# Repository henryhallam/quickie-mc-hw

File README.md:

SiCtroller, also known as Kittyverter, is a sensorless BLDC motor controller
capable of driving low-inductance motors at up to 20 kW.

The power stage uses the Cree/Wolfspeed/Infineon CCS050M12CM2 power module, a
six-pack of 1200V, 50A silicon carbide MOSFETs.  Three Infineon 2ED020I12-F2
dual-channel (half-bridge) gate driver ICs with desaturation fault protection
are powered by six Murata MGJ1 isolated +19V/-5V DC-DC modules.

Current feedback is provided on all three phases by Allegro ACS770 isolated
hall-effect current sensors with a full-scale range of +/-100A.  Phase voltages
are measured via potential dividers with precision RC low-pass filters.

Control is based around the Texas Instruments TMS320F28069M Piccolo DSP MCU,
using the FAST estimator in the Instaspin-FOC ROM library for motor parameter
identification and field-oriented control.

The main external interface is an isolated CAN transceiver.  Some non-isolated
GPIOs and ADC inputs are also brought to external connectors for expansion.

[1]: www.wolfspeed.com/downloads/dl/file/id/189/product/104/ccs050m12cm2.pdf

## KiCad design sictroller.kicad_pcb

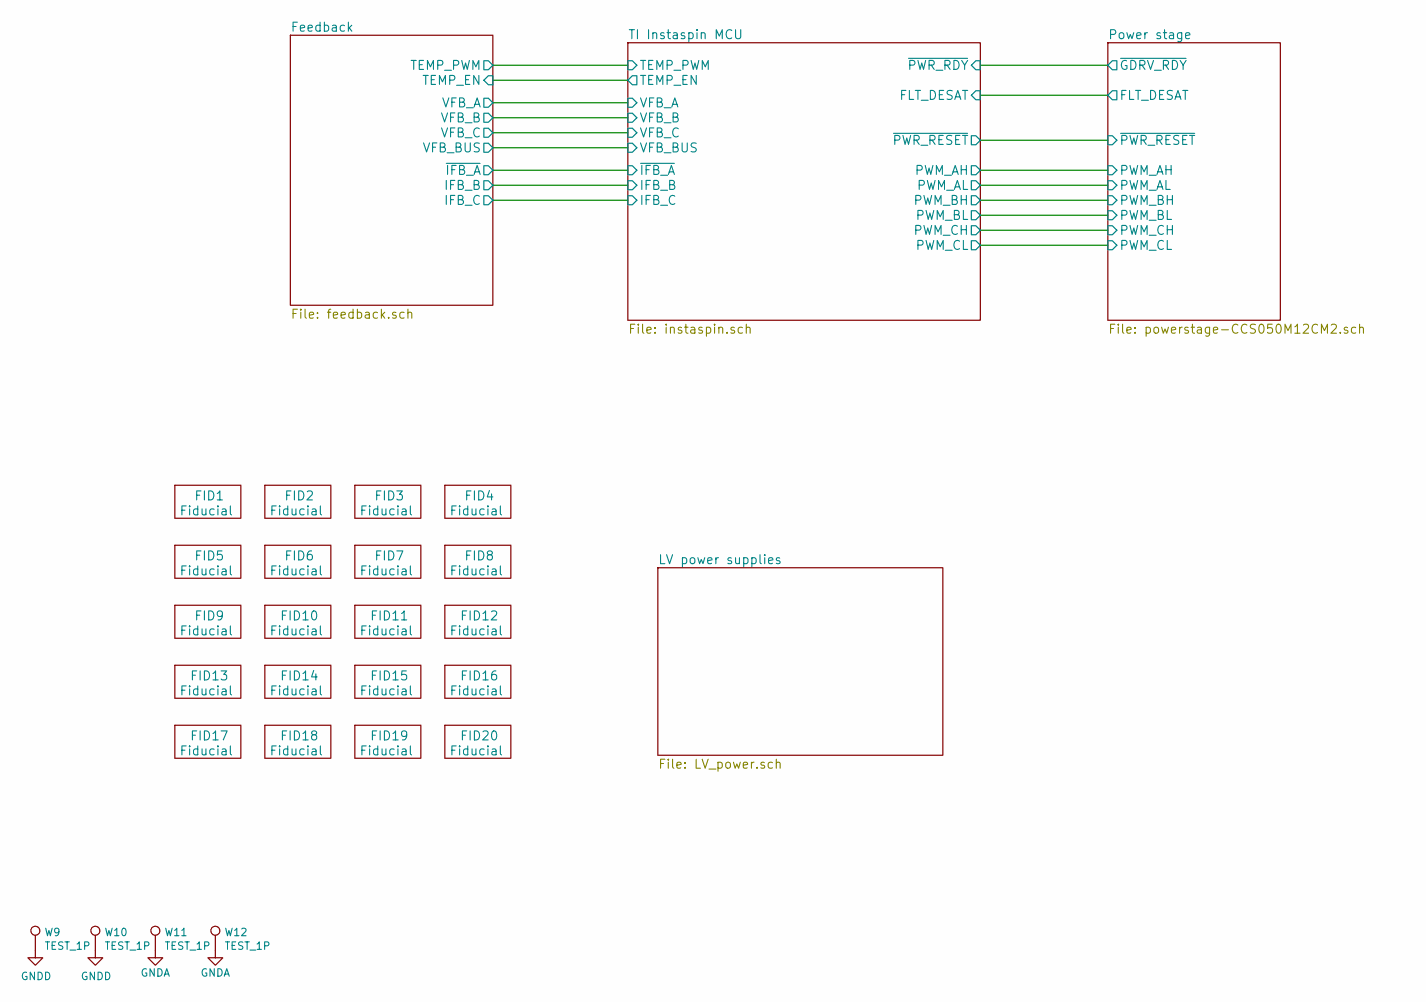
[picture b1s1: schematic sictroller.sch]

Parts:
FID1, FID2, FID3, FID4, FID5, FID6, FID7, FID8, FID9, FID10, FID11, FID12, FID13, FID14, FID15, FID16, FID17, FID18, FID19, FID20: Fiducial; Fiducial_1mm_CopperTop
W9, W10, W11, W12: TEST_1P; Measurement_Point_Round-TH_Small

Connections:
GND: W9.1, W10.1; also elsewhere on the board
GNDA: W11.1, W12.1; also elsewhere on the board

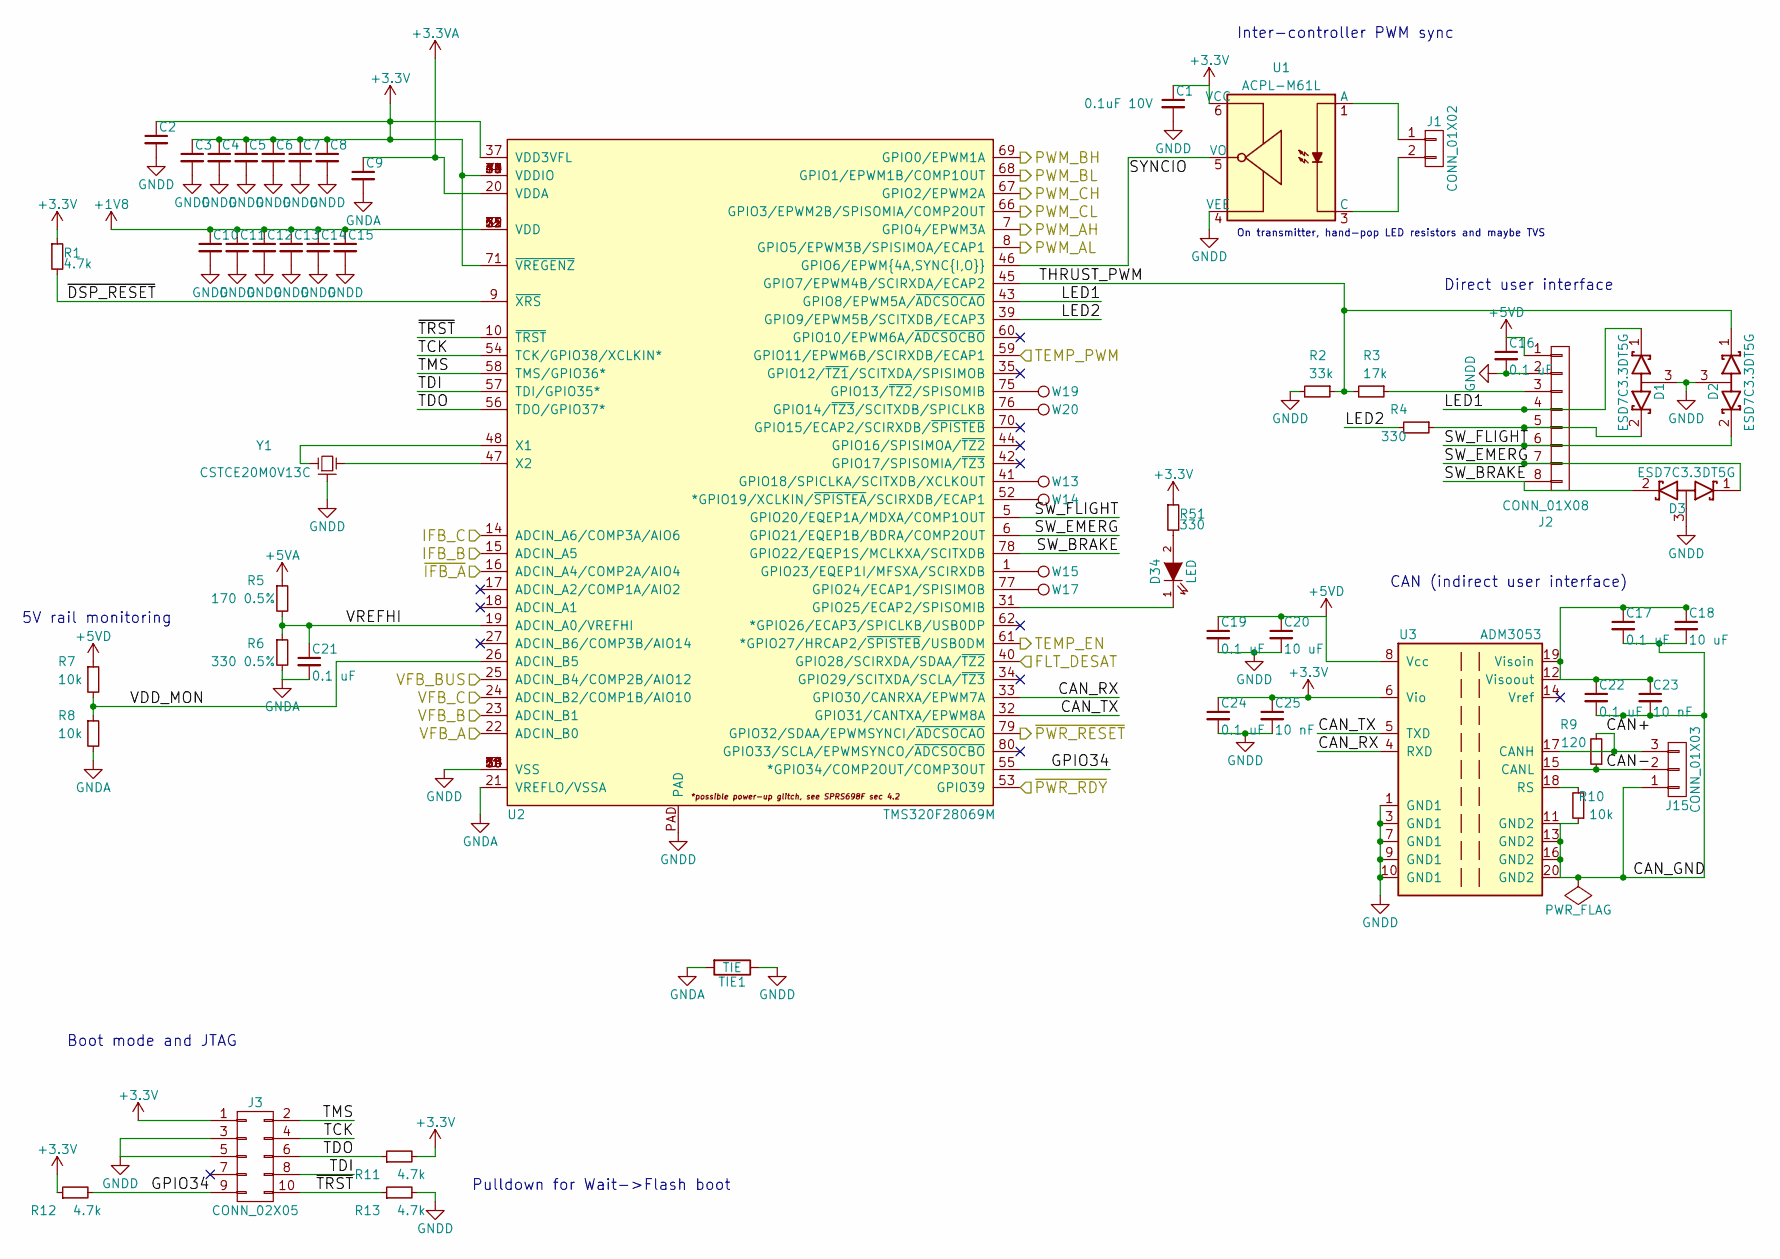
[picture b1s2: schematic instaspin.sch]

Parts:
C1: 0.1uF 10V; C_0402
C2, C3, C4, C5, C6, C7, C8, C9: 2.2uF 10V; C_0603
C10, C11, C12, C13, C14, C15: 2.2uF 6V; C_0402
C16, C17, C19, C21, C22, C24: 0.1 uF; C_0402
C18, C20: 10 uF; C_0805
C23, C25: 10 nF; C_0402
D1, D2, D3: ESD7C3.3DT5G; SOT-723
D34: LED; LED_0603
J1: CONN_01X02; Molex_PicoBlade_53261-0271
J2: CONN_01X08; Molex_PicoBlade_53261-0871
J3: CONN_02X05; FTSH-105-01-L-DV-K
J15: CONN_01X03; Molex_PicoBlade_53261-0371
R1, R11, R12, R13: 4.7k; R_0402
R2: 33k; R_0402
R3: 17k; R_0402
R4, R51: 330; R_0402
R5: 170 0.5%; R_0402
R6: 330 0.5%; R_0402
R7, R8, R10: 10k; R_0402
R9: 120; R_0805
TIE1: TIE; NetTie-_Connected_3x5
U1: ACPL-M61L; ACPL-M61L_SO-5
U2: TMS320F28069M; PFP
U3: ADM3053; SOIC-20W_7.5x12.8mm_Pitch1.27mm
W13, W14, W15, W17, W19, W20: TEST_1P; Measurement_Point_Round-TH_Small
Y1: CSTCE20M0V13C; CSTCE_V13C

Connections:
+1V8: C10.1, C11.1, C12.1, C13.1, C14.1, C15.1, U2.2 (VDD), U2.12 (VDD), U2.29 (VDD), U2.51 (VDD), U2.65 (VDD), U2.72 (VDD); also elsewhere on the board
+3.3VA: C9.1, U2.20 (VDDA); also elsewhere on the board
+3V3: C1.1, C2.1, C3.1, C4.1, C5.1, C6.1, C7.1, C8.1, C24.1, C25.1, J3.1, R1.1, R11.2, R12.1, R51.1, U1.6 (VCC), U2.4 (VDDIO), U2.11 (VDDIO), U2.30 (VDDIO), U2.37 (VDD3VFL), U2.49 (VDDIO), U2.63 (VDDIO), U2.71 (~VREGENZ), U2.74 (VDDIO), U3.6 (Vio); also elsewhere on the board
+5VA: R5.1; also elsewhere on the board
+5VD: C16.1, C19.1, C20.1, J2.1, R7.1, U3.8 (Vcc); also elsewhere on the board
/Feedback/IFB_B: U2.15 (ADCIN_A5); also elsewhere on the board
/Feedback/IFB_C: U2.14 (ADCIN_A6/COMP3A/AIO6); also elsewhere on the board
/Feedback/TEMP_EN: U2.61 (*GPIO27/HRCAP2/~SPISTEB~/USB0DM); also elsewhere on the board
/Feedback/TEMP_PWM: U2.59 (GPIO11/EPWM6B/SCIRXDB/ECAP1); also elsewhere on the board
/Feedback/VFB_A: U2.22 (ADCIN_B0); also elsewhere on the board
/Feedback/VFB_B: U2.23 (ADCIN_B1); also elsewhere on the board
/Feedback/VFB_BUS: U2.25 (ADCIN_B4/COMP2B/AIO12); also elsewhere on the board
/Feedback/VFB_C: U2.24 (ADCIN_B2/COMP1B/AIO10); also elsewhere on the board
/Feedback/~IFB_A: U2.16 (ADCIN_A4/COMP2A/AIO4); also elsewhere on the board
/Power stage/FLT_DESAT: U2.40 (GPIO28/SCIRXDA/SDAA/~TZ2); also elsewhere on the board
/Power stage/PWM_AH: U2.7 (GPIO4/EPWM3A); also elsewhere on the board
/Power stage/PWM_AL: U2.8 (GPIO5/EPWM3B/SPISIMOA/ECAP1); also elsewhere on the board
/Power stage/PWM_BH: U2.69 (GPIO0/EPWM1A); also elsewhere on the board
/Power stage/PWM_BL: U2.68 (GPIO1/EPWM1B/COMP1OUT); also elsewhere on the board
/Power stage/PWM_CH: U2.67 (GPIO2/EPWM2A); also elsewhere on the board
/Power stage/PWM_CL: U2.66 (GPIO3/EPWM2B/SPISOMIA/COMP2OUT); also elsewhere on the board
/Power stage/~GDRV_RDY: U2.53 (GPIO39); also elsewhere on the board
/Power stage/~PWR_RESET: U2.79 (GPIO32/SDAA/EPWMSYNCI/~ADCSOCAO); also elsewhere on the board
/TI Instaspin MCU/CAN+: J15.3, R9.2, U3.17 (CANH)
/TI Instaspin MCU/CAN-: J15.2, R9.1, U3.15 (CANL)
/TI Instaspin MCU/CAN_GND: C17.2, C18.2, C22.2, C23.2, J15.1, R10.1, U3.11 (GND2), U3.13 (GND2), U3.16 (GND2), U3.20 (GND2)
/TI Instaspin MCU/CAN_RX: U2.33 (GPIO30/CANRXA/EPWM7A), U3.4 (RXD)
/TI Instaspin MCU/CAN_TX: U2.32 (GPIO31/CANTXA/EPWM8A), U3.5 (TXD)
/TI Instaspin MCU/GPIO34: J3.9, R12.2, U2.55 (*GPIO34/COMP2OUT/COMP3OUT)
/TI Instaspin MCU/LED1: D1.1 (K), J2.4, U2.43 (GPIO8/EPWM5A/~ADCSOCAO)
/TI Instaspin MCU/LED2: R4.2, U2.39 (GPIO9/EPWM5B/SCITXDB/ECAP3)
/TI Instaspin MCU/SW_BRAKE: D3.2 (K), J2.8, U2.78 (GPIO22/EQEP1S/MCLKXA/SCITXDB)
/TI Instaspin MCU/SW_EMERG: D3.1 (K), J2.7, U2.6 (GPIO21/EQEP1B/BDRA/COMP2OUT)
/TI Instaspin MCU/SW_FLIGHT: D2.2 (K), J2.6, U2.5 (GPIO20/EQEP1A/MDXA/COMP1OUT)
/TI Instaspin MCU/SYNCIO: U1.5 (VO), U2.46 (GPIO6/EPWM{4A,SYNC{I,O}})
/TI Instaspin MCU/TCK: J3.4, U2.54 (TCK/GPIO38/XCLKIN*)
/TI Instaspin MCU/TDI: J3.8, U2.57 (TDI/GPIO35*)
/TI Instaspin MCU/TDO: J3.6, R11.1, U2.56 (TDO/GPIO37*)
/TI Instaspin MCU/THRUST_PWM: D2.1 (K), R2.1, R3.2, U2.45 (GPIO7/EPWM4B/SCIRXDA/ECAP2)
/TI Instaspin MCU/TMS: J3.2, U2.58 (TMS/GPIO36*)
/TI Instaspin MCU/VDD_MON: R7.2, R8.1, U2.26 (ADCIN_B5)
/TI Instaspin MCU/VREFHI: C21.1, R5.2, R6.1, U2.19 (ADCIN_A0/VREFHI)
/TI Instaspin MCU/~DSP_RESET: R1.2, U2.9 (~XRS)
/TI Instaspin MCU/~TRST: J3.10, R13.1, U2.10 (~TRST)
GND: C1.2, C2.2, C3.2, C4.2, C5.2, C6.2, C7.2, C8.2, C10.2, C11.2, C12.2, C13.2, C14.2, C15.2, C16.2, C19.2, C20.2, C24.2, C25.2, D1.3 (A), D2.3 (A), D3.3 (A), J2.2, J3.3, J3.5, R2.2, R13.2, TIE1.1, U1.4 (VEE), U2.3 (VSS), U2.13 (VSS), U2.28 (VSS), U2.38 (VSS), U2.50 (VSS), U2.64 (VSS), U2.73 (VSS), U2.PAD, U3.1 (GND1), U3.3 (GND1), U3.7 (GND1), U3.9 (GND1), U3.10 (GND1), Y1.2 (common); also elsewhere on the board
GNDA: C9.2, C21.2, R6.2, R8.2, TIE1.2, U2.21 (VREFLO/VSSA); also elsewhere on the board
unnamed: C17.1, C18.1, C22.1, C23.1, U3.12 (Visoout), U3.19 (Visoin)
unnamed: D1.2 (K), J2.5, R4.1
unnamed: D34.1 (K), U2.31 (GPIO25/ECAP2/SPISOMIB)
unnamed: D34.2 (A), R51.2
unnamed: J1.1, U1.1 (A)
unnamed: J1.2, U1.3 (C)
unnamed: J2.3, R3.1
unnamed: R10.2, U3.18 (RS)
unnamed: U2.1 (GPIO23/EQEP1I/MFSXA/SCIRXDB), W15.1
unnamed: U2.41 (GPIO18/SPICLKA/SCITXDB/XCLKOUT), W13.1
unnamed: U2.47 (X2), Y1.3 (2)
unnamed: U2.48 (X1), Y1.1
unnamed: U2.52 (*GPIO19/XCLKIN/~SPISTEA~/SCIRXDB/ECAP1), W14.1
unnamed: U2.75 (GPIO13/~TZ2~/SPISOMIB), W19.1
unnamed: U2.76 (GPIO14/~TZ3~/SCITXDB/SPICLKB), W20.1
unnamed: U2.77 (GPIO24/ECAP1/SPISIMOB), W17.1

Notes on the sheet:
Boot mode and JTAG
On transmitter, hand-pop LED resistors and maybe TVS
Inter-controller PWM sync
Direct user interface
CAN (indirect user interface)
5V rail monitoring
Pulldown for Wait->Flash boot

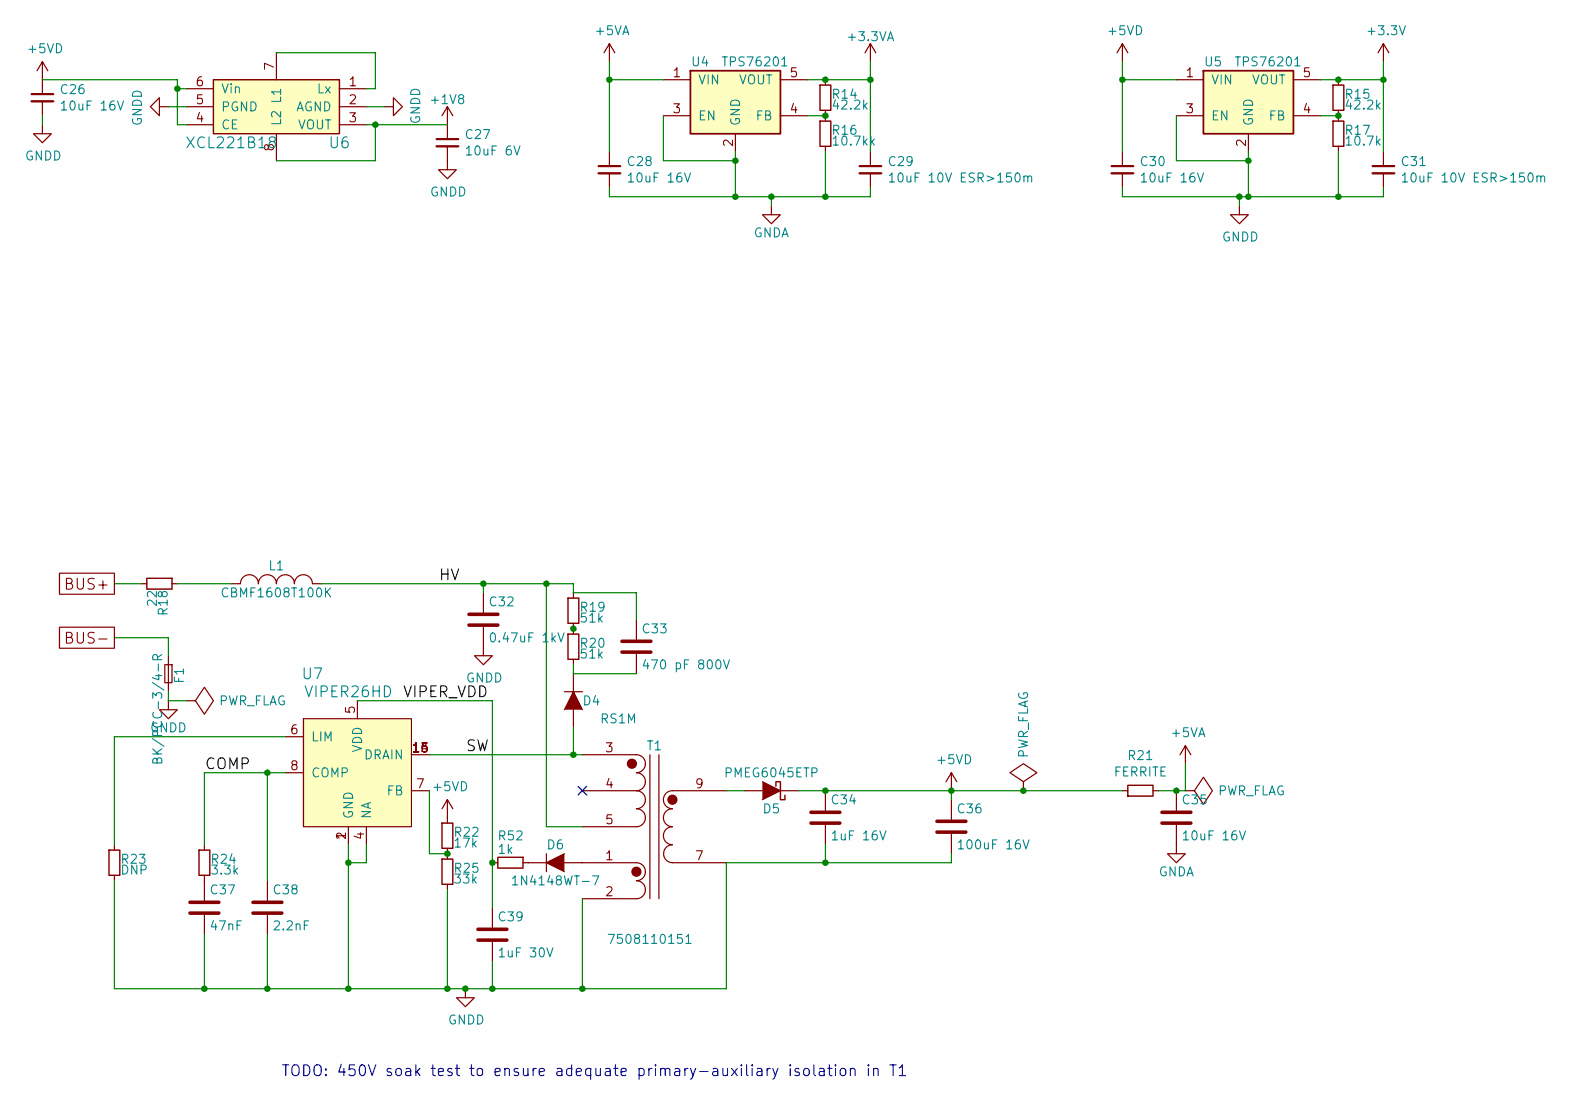
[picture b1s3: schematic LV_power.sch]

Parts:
C26, C28, C30, C35: 10uF 16V; C_0805
C27: 10uF 6V; C_0603
C29, C31: 10uF 10V ESR>150m; C_0603
C32: 0.47uF 1kV; C_2220
C33: 470 pF 800V; C_1206
C34: 1uF 16V; C_0603
C36: 100uF 16V; C_6x5
C37: 47nF; C_0402
C38: 2.2nF; C_0402
C39: 1uF 30V; C_0603
D4: RS1M; SMA_Standard
D5: PMEG6045ETP; SOD-128
D6: 1N4148WT-7; SOD-523
F1: BK/PCC-3/4-R; Fuse_TE5_Littlefuse-395Series
L1: CBMF1608T100K; R_0603
R14, R15: 42.2k; R_0402
R16: 10.7kk; R_0402
R17: 10.7k; R_0402
R18: 22; R_0603
R19, R20: 51k; R_1206
R21: FERRITE; R_0805
R22: 17k; R_0402
R23: DNP; R_0402
R24: 3.3k; R_0402
R25: 33k; R_0402
R52: 1k; R_0402
T1: 7508110151; WE-7508110151
U4, U5: TPS76201; SOT-23-5
U6: XCL221B18; XCL22x
U7: VIPER26HD; SOIC-16_3.9x9.9mm_Pitch1.27mm

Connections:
+1V8: C27.1, U6.3 (VOUT), U6.8 (L2); also elsewhere on the board
+3.3VA: C29.1, R14.1, U4.5 (VOUT); also elsewhere on the board
+3V3: C31.1, R15.1, U5.5 (VOUT); also elsewhere on the board
+5VA: C28.1, C35.1, R21.2, U4.1 (VIN); also elsewhere on the board
+5VD: C26.1, C30.1, C34.1, C36.1, D5.1 (K), R21.1, R22.1, U5.1 (VIN), U6.4 (CE), U6.6 (Vin); also elsewhere on the board
/LV power supplies/COMP: C38.1, R24.1, U7.8 (COMP)
/LV power supplies/HV: C32.1, C33.1, L1.2, R19.1, T1.5 (PR2)
/LV power supplies/SW: D4.2 (A), T1.3 (PR1), U7.13 (DRAIN), U7.14 (DRAIN), U7.15 (DRAIN), U7.16 (DRAIN)
/LV power supplies/VIPER_VDD: C39.1, R52.2, U7.5 (VDD)
BUS+: R18.2; also elsewhere on the board
BUS-: F1.1; also elsewhere on the board
GND: C26.2, C27.2, C30.2, C31.2, C32.2, C34.2, C36.2, C37.2, C38.2, C39.2, F1.2, R17.2, R23.2, R25.2, T1.2 (AUX2), T1.7 (S1), U5.2 (GND), U5.3 (EN), U6.2 (AGND), U6.5 (PGND), U6.PAD, U7.1 (GND), U7.2 (GND), U7.4 (NA); also elsewhere on the board
GNDA: C28.2, C29.2, C35.2, R16.2, U4.2 (GND), U4.3 (EN); also elsewhere on the board
unnamed: C33.2, D4.1 (K), R20.2
unnamed: C37.1, R24.2
unnamed: D5.2 (A), T1.9 (S2)
unnamed: D6.1 (K), R52.1
unnamed: D6.2 (A), T1.1 (AUX1)
unnamed: L1.1, R18.1
unnamed: R14.2, R16.1, U4.4 (FB)
unnamed: R15.2, R17.1, U5.4 (FB)
unnamed: R19.2, R20.1
unnamed: R22.2, R25.1, U7.7 (FB)
unnamed: R23.1, U7.6 (LIM)
unnamed: U6.1 (Lx), U6.7 (L1)

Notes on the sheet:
TODO: 450V soak test to ensure adequate primary-auxiliary isolation in T1

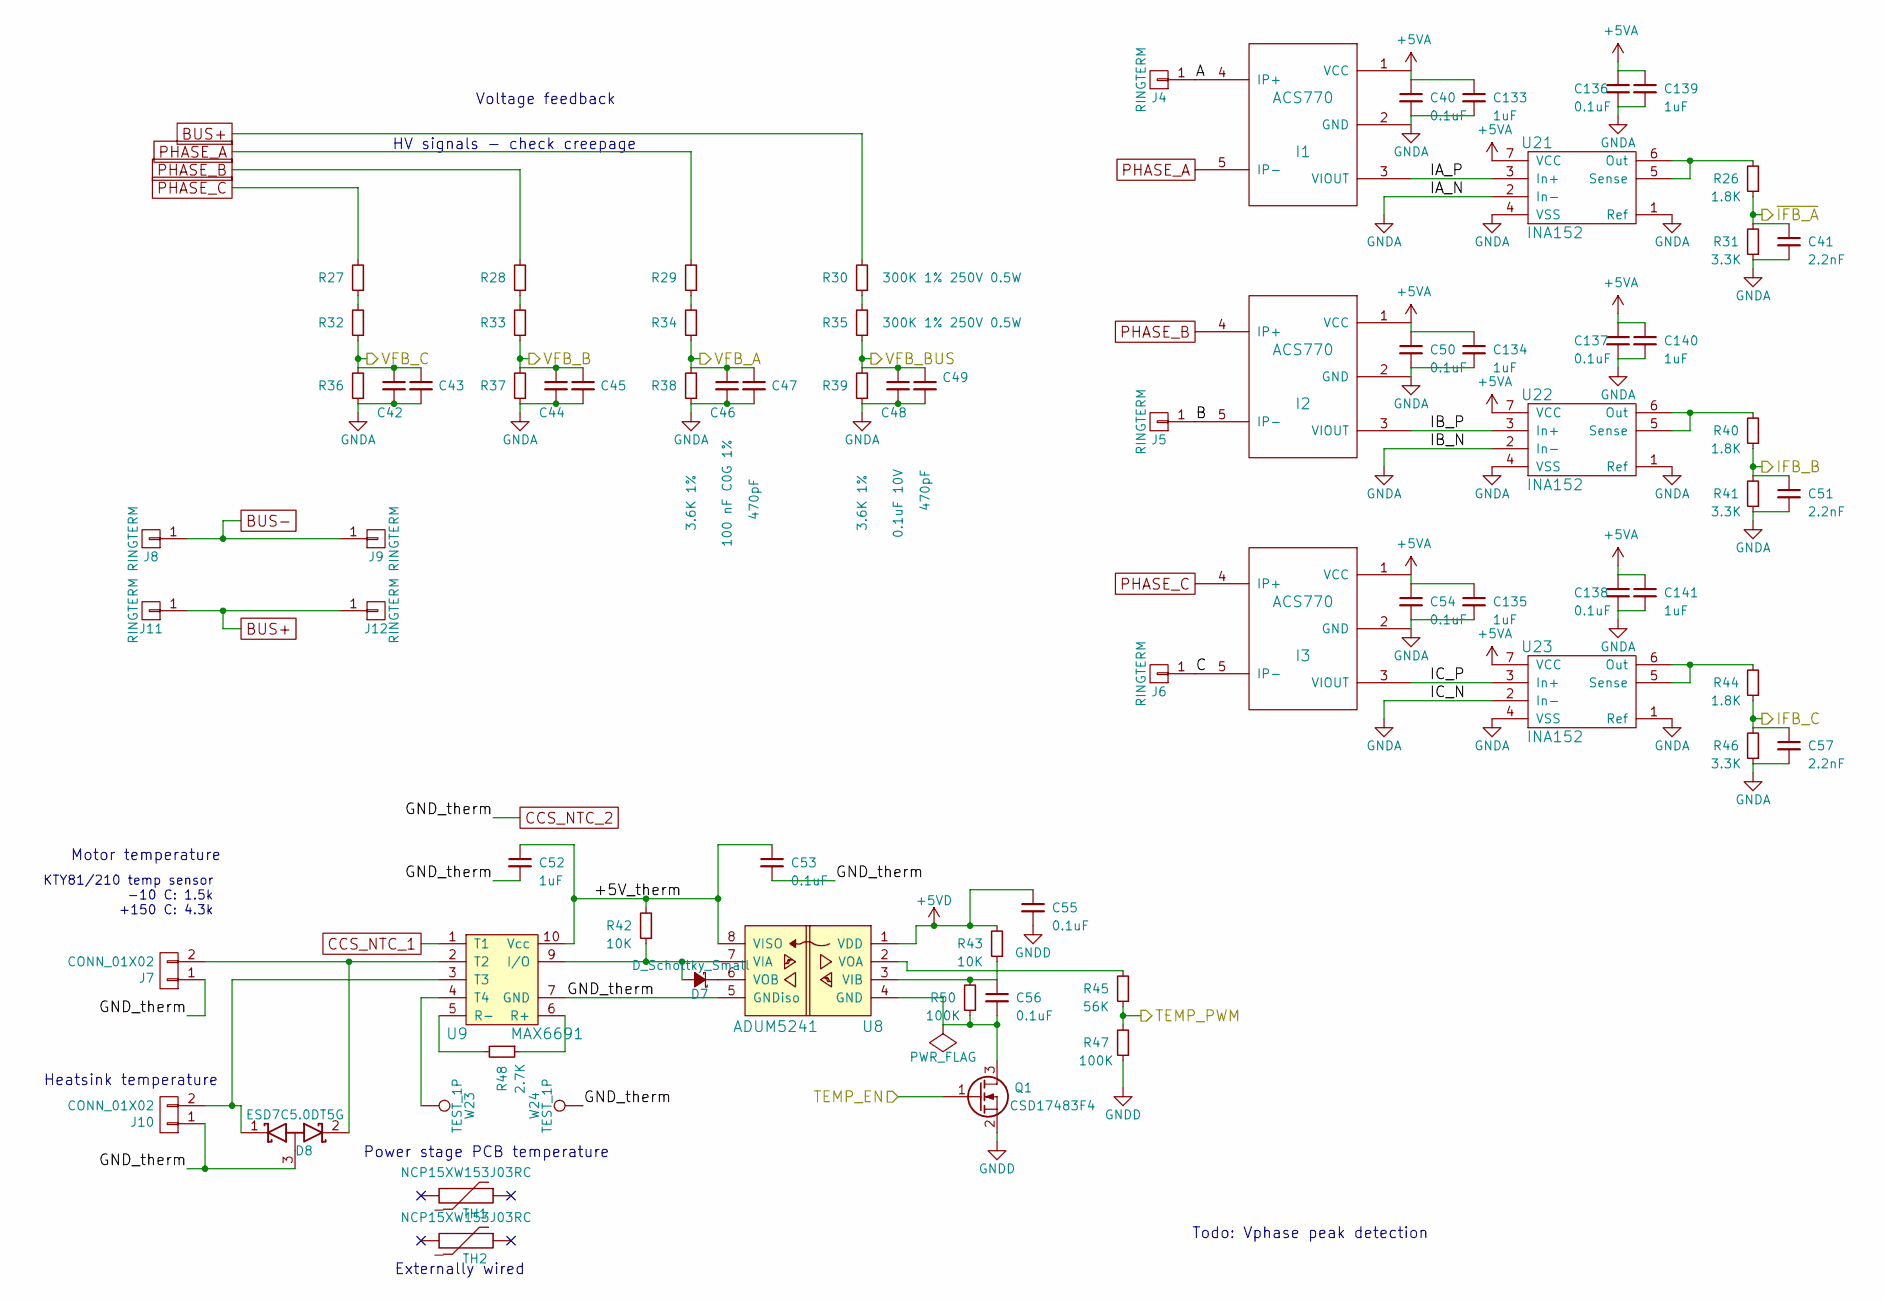
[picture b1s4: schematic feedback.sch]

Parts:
C40, C50, C53, C54, C55, C56, C136, C137, C138: 0.1uF; C_0402
C41, C51, C57: 2.2nF; C_0402
C42, C44, C46: 100 nF C0G 1%; C_1210
C43, C45, C47, C49: 470pF; C_0402
C48: 0.1uF 10V; C_0402
C52, C133, C134, C135, C139, C140, C141: 1uF; C_0603
D7: D_Schottky_Small; SOD-523
D8: ESD7C5.0DT5G; SOT-723
I1, I2, I3: ACS770
J4, J5, J6, J8, J9, J11, J12: RINGTERM; B6A-PCB
J7, J10: CONN_01X02; Molex_PicoBlade_53261-0271
Q1: CSD17483F4; FEMTOFET_YJC_YJJ
R26, R40, R44: 1.8K; R_0402
R27, R28, R29, R30, R32, R33, R34, R35: 300K 1% 250V 0.5W; R_0805
R31, R41, R46: 3.3K; R_0402
R36, R37, R38, R39: 3.6K 1%; R_0402
R42, R43: 10K; R_0402
R45: 56K; R_0402
R47, R50: 100K; R_0402
R48: 2.7K; R_0402
TH1, TH2: NCP15XW153J03RC; R_0402_extwire
U8: ADUM5241; SOIC-8_3.9x4.9mm_Pitch1.27mm
U9: MAX6691; MSOP-10_3x3mm_Pitch0.5mm
U21, U22, U23: INA152; MSOP-8_3x3mm_Pitch0.65mm
W23, W24: TEST_1P; Measurement_Point_Round-TH_Small

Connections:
+5VA: C40.1, C50.1, C54.1, C133.1, C134.1, C135.1, C136.1, C137.1, C138.1, C139.1, C140.1, C141.1, I1.1 (VCC), I2.1 (VCC), I3.1 (VCC), U21.7 (VCC), U22.7 (VCC), U23.7 (VCC); also elsewhere on the board
+5VD: C55.1, R43.2, U8.1 (VDD); also elsewhere on the board
/Feedback/+5V_therm: C52.1, C53.1, R42.2, U8.8 (VISO), U9.10 (Vcc)
/Feedback/A: I1.4 (IP+), J4.1
/Feedback/B: I2.5 (IP-), J5.1
/Feedback/C: I3.5 (IP-), J6.1
/Feedback/IA_P: I1.3 (VIOUT), U21.3 (In+)
/Feedback/IB_P: I2.3 (VIOUT), U22.3 (In+)
/Feedback/IC_P: I3.3 (VIOUT), U23.3 (In+)
/Feedback/IFB_B: C51.1, R40.1, R41.2; also elsewhere on the board
/Feedback/IFB_C: C57.1, R44.1, R46.2; also elsewhere on the board
/Feedback/TEMP_EN: Q1.1 (G); also elsewhere on the board
/Feedback/TEMP_PWM: R45.1, R47.2; also elsewhere on the board
/Feedback/VFB_A: C46.1, C47.1, R34.1, R38.2; also elsewhere on the board
/Feedback/VFB_B: C44.1, C45.1, R33.1, R37.2; also elsewhere on the board
/Feedback/VFB_BUS: C48.1, C49.1, R35.1, R39.2; also elsewhere on the board
/Feedback/VFB_C: C42.1, C43.1, R32.1, R36.2; also elsewhere on the board
/Feedback/~IFB_A: C41.1, R26.1, R31.2; also elsewhere on the board
BUS+: J11.1, J12.1, R30.2; also elsewhere on the board
BUS-: J8.1, J9.1; also elsewhere on the board
CCS_NTC_1: U9.1 (T1); also elsewhere on the board
CCS_NTC_2: C52.2, C53.2, D8.3 (A), J7.1, J10.1, U8.5 (GNDiso), U9.7 (GND), W24.1; also elsewhere on the board
GND: C55.2, Q1.2 (S), R47.1; also elsewhere on the board
GNDA: C40.2, C41.2, C42.2, C43.2, C44.2, C45.2, C46.2, C47.2, C48.2, C49.2, C50.2, C51.2, C54.2, C57.2, C133.2, C134.2, C135.2, C136.2, C137.2, C138.2, C139.2, C140.2, C141.2, I1.2 (GND), I2.2 (GND), I3.2 (GND), R31.1, R36.1, R37.1, R38.1, R39.1, R41.1, R46.1, U21.1 (Ref), U21.2 (In-), U21.4 (VSS), U22.1 (Ref), U22.2 (In-), U22.4 (VSS), U23.1 (Ref), U23.2 (In-), U23.4 (VSS); also elsewhere on the board
unnamed: C56.1, R43.1, R50.2, U8.3 (VIB)
unnamed: C56.2, Q1.3 (D), R50.1, U8.4 (GND)
unnamed: D7.1 (K), U8.6 (VOB)
unnamed: D7.2 (A), R42.1, U8.7 (VIA), U9.9 (I/O)
unnamed: D8.1 (K), J10.2, U9.3 (T3)
unnamed: D8.2 (K), J7.2, U9.2 (T2)
unnamed: R26.2, U21.5 (Sense), U21.6 (Out)
unnamed: R27.1, R32.2
unnamed: R28.1, R33.2
unnamed: R29.1, R34.2
unnamed: R30.1, R35.2
unnamed: R40.2, U22.5 (Sense), U22.6 (Out)
unnamed: R44.2, U23.5 (Sense), U23.6 (Out)
unnamed: R45.2, U8.2 (VOA)
unnamed: R48.1, U9.6 (R+)
unnamed: R48.2, U9.5 (R-)
unnamed: U9.4 (T4), W23.1
PHASE_A: I1.5 (IP-), R29.2; also elsewhere on the board
PHASE_B: I2.4 (IP+), R28.2; also elsewhere on the board
PHASE_C: I3.4 (IP+), R27.2; also elsewhere on the board

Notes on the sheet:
HV signals - check creepage
Todo: Vphase peak detection
KTY81/210 temp sensor -10 C: 1.5k +150 C: 4.3k
Voltage feedback
Motor temperature
Heatsink temperature
Power stage PCB temperature
Externally wired

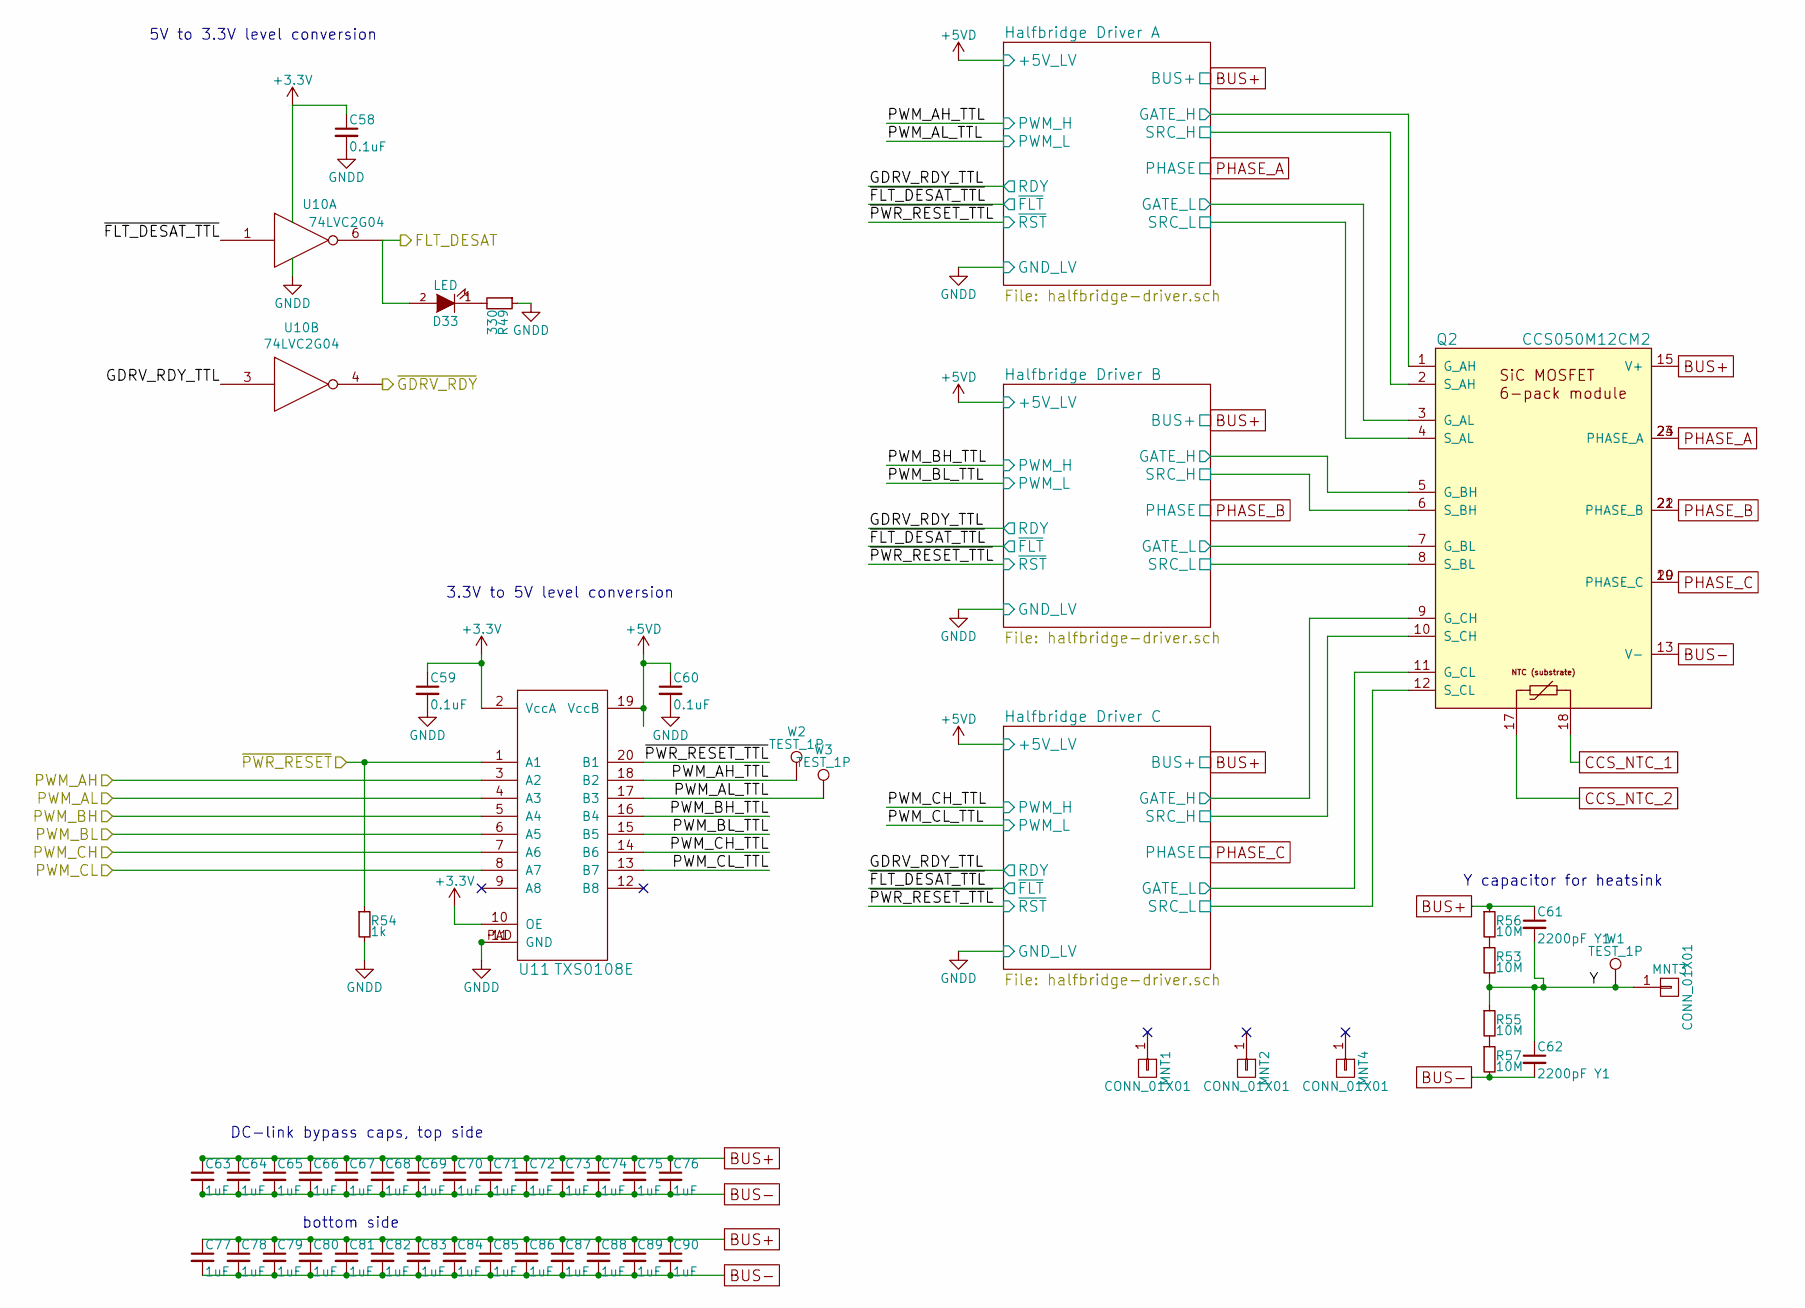
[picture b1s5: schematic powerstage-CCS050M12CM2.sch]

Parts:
C58, C59, C60: 0.1uF; C_0402
C61, C62: 2200pF Y1; CAP_ERP610_12-5MM; MPN ERP610W222MERU
C63, C64, C65, C66, C67, C68, C69, C70, C71, C72, C73, C74, C75, C76: 1uF; Ceralink-L-viastitch
C77, C78, C79, C80, C81, C82, C83, C84, C85, C86, C87, C88, C89, C90: 1uF; Ceralink-L
D33: LED; LED_0603
MNT1, MNT2, MNT3, MNT4: CONN_01X01; MountingHole_3mm_Pad_Via
Q2: CCS050M12CM2; 6pack-45mm
R49: 330; R_0402
R53, R55, R56, R57: 10M; R_0805
R54: 1k; R_0402
U10: 74LVC2G04; TSOT-6-MK06A
U11: TXS0108E; VQFN-20
W1: TEST_1P; Measurement_Point_Round-TH_Big
W2, W3: TEST_1P; Measurement_Point_Round-TH_Small

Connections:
+3V3: C58.1, C59.1, U10.5 (VCC), U11.2 (VccA), U11.10 (OE); also elsewhere on the board
+5VD: C60.1, U11.19 (VccB); also elsewhere on the board
/Power stage/FLT_DESAT: D33.2 (A), U10.6; also elsewhere on the board
/Power stage/Halfbridge Driver A/GATE_H: Q2.1 (G_AH); also elsewhere on the board
/Power stage/Halfbridge Driver A/GATE_L: Q2.3 (G_AL); also elsewhere on the board
/Power stage/Halfbridge Driver A/PWM_H: U11.18 (B2), W2.1; also elsewhere on the board
/Power stage/Halfbridge Driver A/PWM_L: U11.17 (B3), W3.1; also elsewhere on the board
/Power stage/Halfbridge Driver A/RDY: U10.3; also elsewhere on the board
/Power stage/Halfbridge Driver A/SRC_H: Q2.2 (S_AH); also elsewhere on the board
/Power stage/Halfbridge Driver A/SRC_L: Q2.4 (S_AL); also elsewhere on the board
/Power stage/Halfbridge Driver A/~FLT: U10.1; also elsewhere on the board
/Power stage/Halfbridge Driver A/~RST: U11.20 (B1); also elsewhere on the board
/Power stage/Halfbridge Driver B/GATE_H: Q2.5 (G_BH); also elsewhere on the board
/Power stage/Halfbridge Driver B/GATE_L: Q2.7 (G_BL); also elsewhere on the board
/Power stage/Halfbridge Driver B/PWM_H: U11.16 (B4); also elsewhere on the board
/Power stage/Halfbridge Driver B/PWM_L: U11.15 (B5); also elsewhere on the board
/Power stage/Halfbridge Driver B/SRC_H: Q2.6 (S_BH); also elsewhere on the board
/Power stage/Halfbridge Driver B/SRC_L: Q2.8 (S_BL); also elsewhere on the board
/Power stage/Halfbridge Driver C/GATE_H: Q2.9 (G_CH); also elsewhere on the board
/Power stage/Halfbridge Driver C/GATE_L: Q2.11 (G_CL); also elsewhere on the board
/Power stage/Halfbridge Driver C/PWM_H: U11.14 (B6); also elsewhere on the board
/Power stage/Halfbridge Driver C/PWM_L: U11.13 (B7); also elsewhere on the board
/Power stage/Halfbridge Driver C/SRC_H: Q2.10 (S_CH); also elsewhere on the board
/Power stage/Halfbridge Driver C/SRC_L: Q2.12 (S_CL); also elsewhere on the board
/Power stage/PWM_AH: U11.3 (A2); also elsewhere on the board
/Power stage/PWM_AL: U11.4 (A3); also elsewhere on the board
/Power stage/PWM_BH: U11.5 (A4); also elsewhere on the board
/Power stage/PWM_BL: U11.6 (A5); also elsewhere on the board
/Power stage/PWM_CH: U11.7 (A6); also elsewhere on the board
/Power stage/PWM_CL: U11.8 (A7); also elsewhere on the board
/Power stage/Y: C61.2, C62.1, MNT3.1, R53.2, R55.1, W1.1
/Power stage/~GDRV_RDY: U10.4; also elsewhere on the board
/Power stage/~PWR_RESET: R54.1, U11.1 (A1); also elsewhere on the board
BUS+: C61.1, C63.1, C64.1, C65.1, C66.1, C67.1, C68.1, C69.1, C70.1, C71.1, C72.1, C73.1, C74.1, C75.1, C76.1, C77.1, C78.1, C79.1, C80.1, C81.1, C82.1, C83.1, C84.1, C85.1, C86.1, C87.1, C88.1, C89.1, C90.1, Q2.15 (V+), Q2.16 (V+), Q2.25 (V+), Q2.26 (V+), R56.1; also elsewhere on the board
BUS-: C62.2, C63.2, C64.2, C65.2, C66.2, C67.2, C68.2, C69.2, C70.2, C71.2, C72.2, C73.2, C74.2, C75.2, C76.2, C77.2, C78.2, C79.2, C80.2, C81.2, C82.2, C83.2, C84.2, C85.2, C86.2, C87.2, C88.2, C89.2, C90.2, Q2.13 (V-), Q2.14 (V-), Q2.27 (V-), Q2.28 (V-), R57.2; also elsewhere on the board
CCS_NTC_1: Q2.18; also elsewhere on the board
CCS_NTC_2: Q2.17; also elsewhere on the board
GND: C58.2, C59.2, C60.2, R49.1, R54.2, U10.2 (GND), U11.11 (GND), U11.PAD (GND); also elsewhere on the board
unnamed: D33.1 (K), R49.2
unnamed: R53.1, R56.2
unnamed: R55.2, R57.1
PHASE_A: Q2.23 (PHASE_A), Q2.24 (PHASE_A); also elsewhere on the board
PHASE_B: Q2.21 (PHASE_B), Q2.22 (PHASE_B); also elsewhere on the board
PHASE_C: Q2.19 (PHASE_C), Q2.20 (PHASE_C); also elsewhere on the board

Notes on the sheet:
5V to 3.3V level conversion
3.3V to 5V level conversion
Y capacitor for heatsink
DC-link bypass caps, top side
bottom side
